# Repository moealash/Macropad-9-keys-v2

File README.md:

<h1 align="center">
  <br>
  
  <br>
  Finite's Macroboard
  <br>
</h1>
<h4 align="center">
A 3x3 MacroPad for faster macros
</h4>

<h2>
Explanation 
  
</h2>

<h4>
This is a Macroboard that has 9 keys to get around my pc faster with macros. I made it because I want to see if I have what it takes to have a future with electronics.
</h4>
<h2>
  
</h2>
<h2>Parts</h2>

<h3>

- **XIAO RP2040** It is the Usb type C connnecter
  
- **9 Cherry MX switches** It sends an input to the PCB
  
- **9 keycaps** It is a cover for the switchs
  
- **Custom 3d Case** It holds and protects the PCB
  
- **Custom PCB** It connects the wires to the electronics
</h3>
<h2>
  
</h2>

<h2>PCB</h2>
<h3>The PCB was made in kicad it took me 1 hour and 30 minutes because I didnt know how to add a XIAO RP2040.</h3>
<h2>
  
</h2>

<h2>
  
</h2>
<h2>PCB layers</h2>
<h3>The Front is for the powering of the electronics it is in the red it took me 1 hour .</h3>

<h3>The back is for the Gnd of the electronics it is in the red it took me 20 minutes.</h3>

<h2>3d Print</h2>
<h3>3d Print was made in fusion 360 it took me 2 hours and 30 minutes. </h3>

<h3>
- <a href="https://www.kicad.org/">KiCad</a><br>
- <a href="https://www.autodesk.com/products/fusion-360/overview">Fusion 360</a> for 3D renders<br>
- <a href="https://blueprint.hackclub.com/projects/491">Hack Club Blueprint</a>
</h3>

## Bill of Materials

| Part | Quantity | Link |
|-----|-----|-----|
| Seeed XIAO RP2040 | 1 | https://www.seeedstudio.com/XIAO-RP2040-p-5026.html |
| Cherry MX Switch | 9 | https://www.amazon.com |
| Keycaps | 9 | https://www.amazon.com |

<h3>
Readme was inspired by <a href="https://github.com/notaroomba">notaroomba</a><br>
Everything was made by FiniteHorizon.
</h3>

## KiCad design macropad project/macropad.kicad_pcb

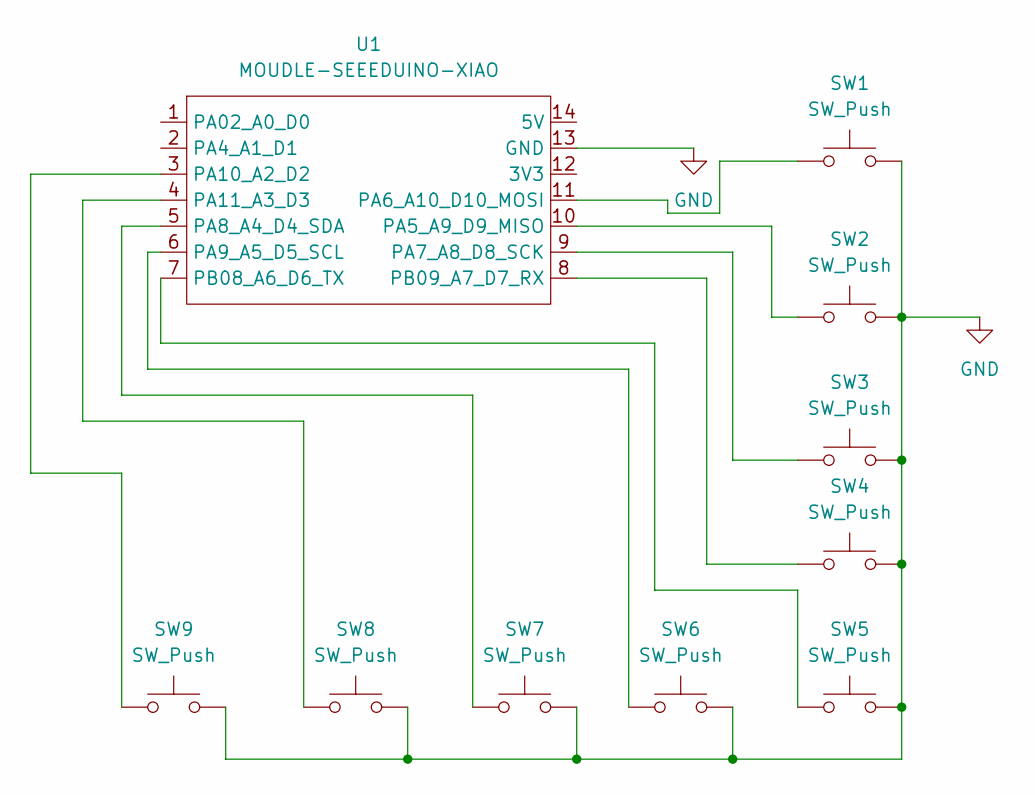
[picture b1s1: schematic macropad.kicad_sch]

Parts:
SW1, SW2, SW3, SW4, SW5, SW6, SW7, SW8, SW9: SW_Push; SW_Cherry_MX_1.00u_PCB
U1: MOUDLE-SEEEDUINO-XIAO; XIAO-RP2040-DIP

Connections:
GND: SW1.2, SW2.2, SW3.2, SW4.2, SW5.2, SW6.2, SW7.2, SW8.2, SW9.2, U1.13 (GND)
unnamed: SW2.1, U1.10 (PA5_A9_D9_MISO)
unnamed: SW1.1, U1.11 (PA6_A10_D10_MOSI)
unnamed: SW3.1, U1.9 (PA7_A8_D8_SCK)
unnamed: SW7.1, U1.5 (PA8_A4_D4_SDA)
unnamed: SW6.1, U1.6 (PA9_A5_D5_SCL)
unnamed: SW9.1, U1.3 (PA10_A2_D2)
unnamed: SW8.1, U1.4 (PA11_A3_D3)
unnamed: SW5.1, U1.7 (PB08_A6_D6_TX)
unnamed: SW4.1, U1.8 (PB09_A7_D7_RX)

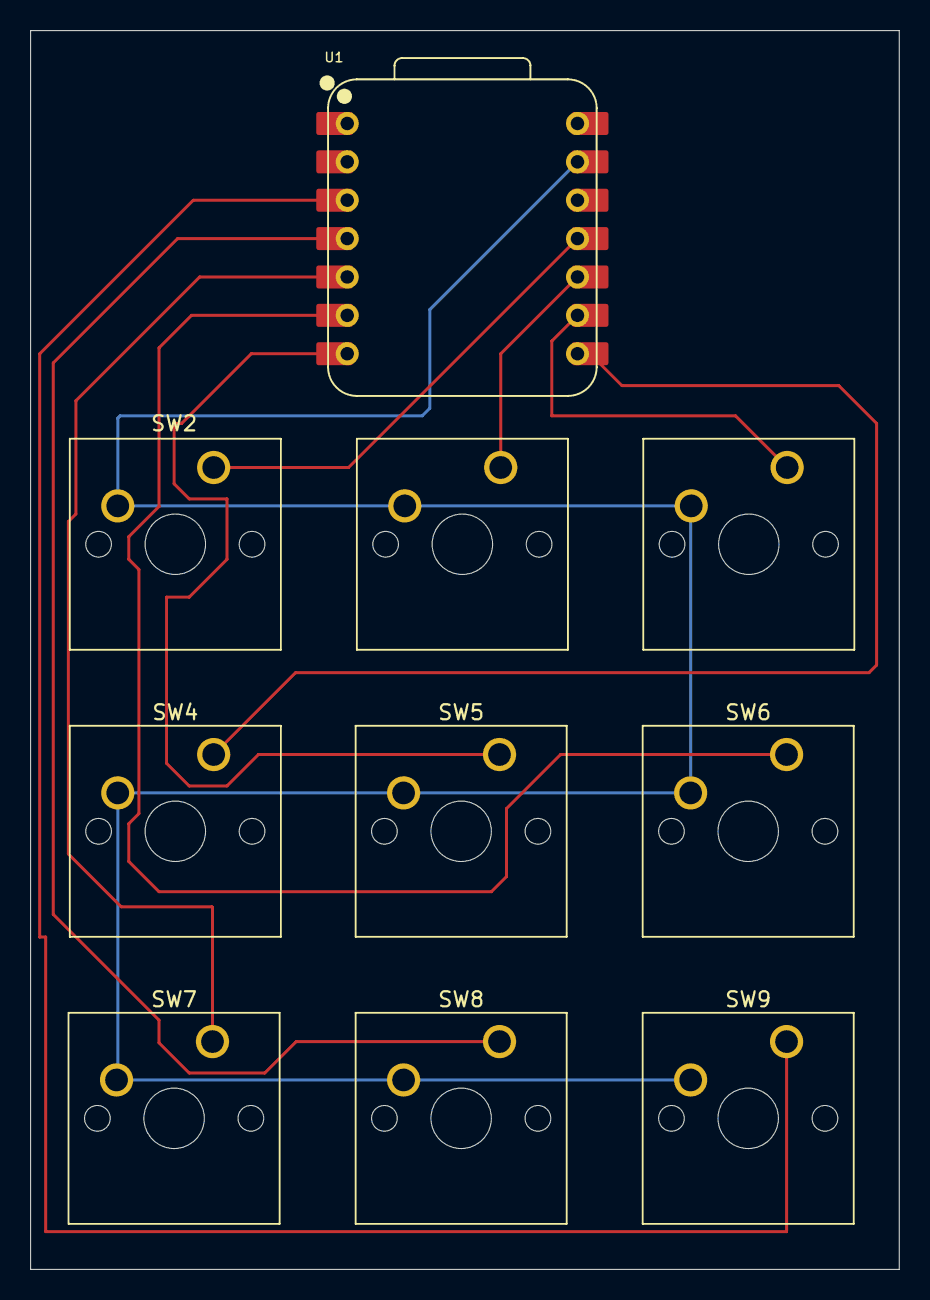
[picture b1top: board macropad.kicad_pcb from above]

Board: 2 copper layers, 57.5 x 82.0 mm, 10 parts (0 on the bottom side), 10 nets.

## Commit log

2026-03-07 All the files for kicad and case for the blueprint
2026-03-08 README.md
2026-03-08 For pcb Way
